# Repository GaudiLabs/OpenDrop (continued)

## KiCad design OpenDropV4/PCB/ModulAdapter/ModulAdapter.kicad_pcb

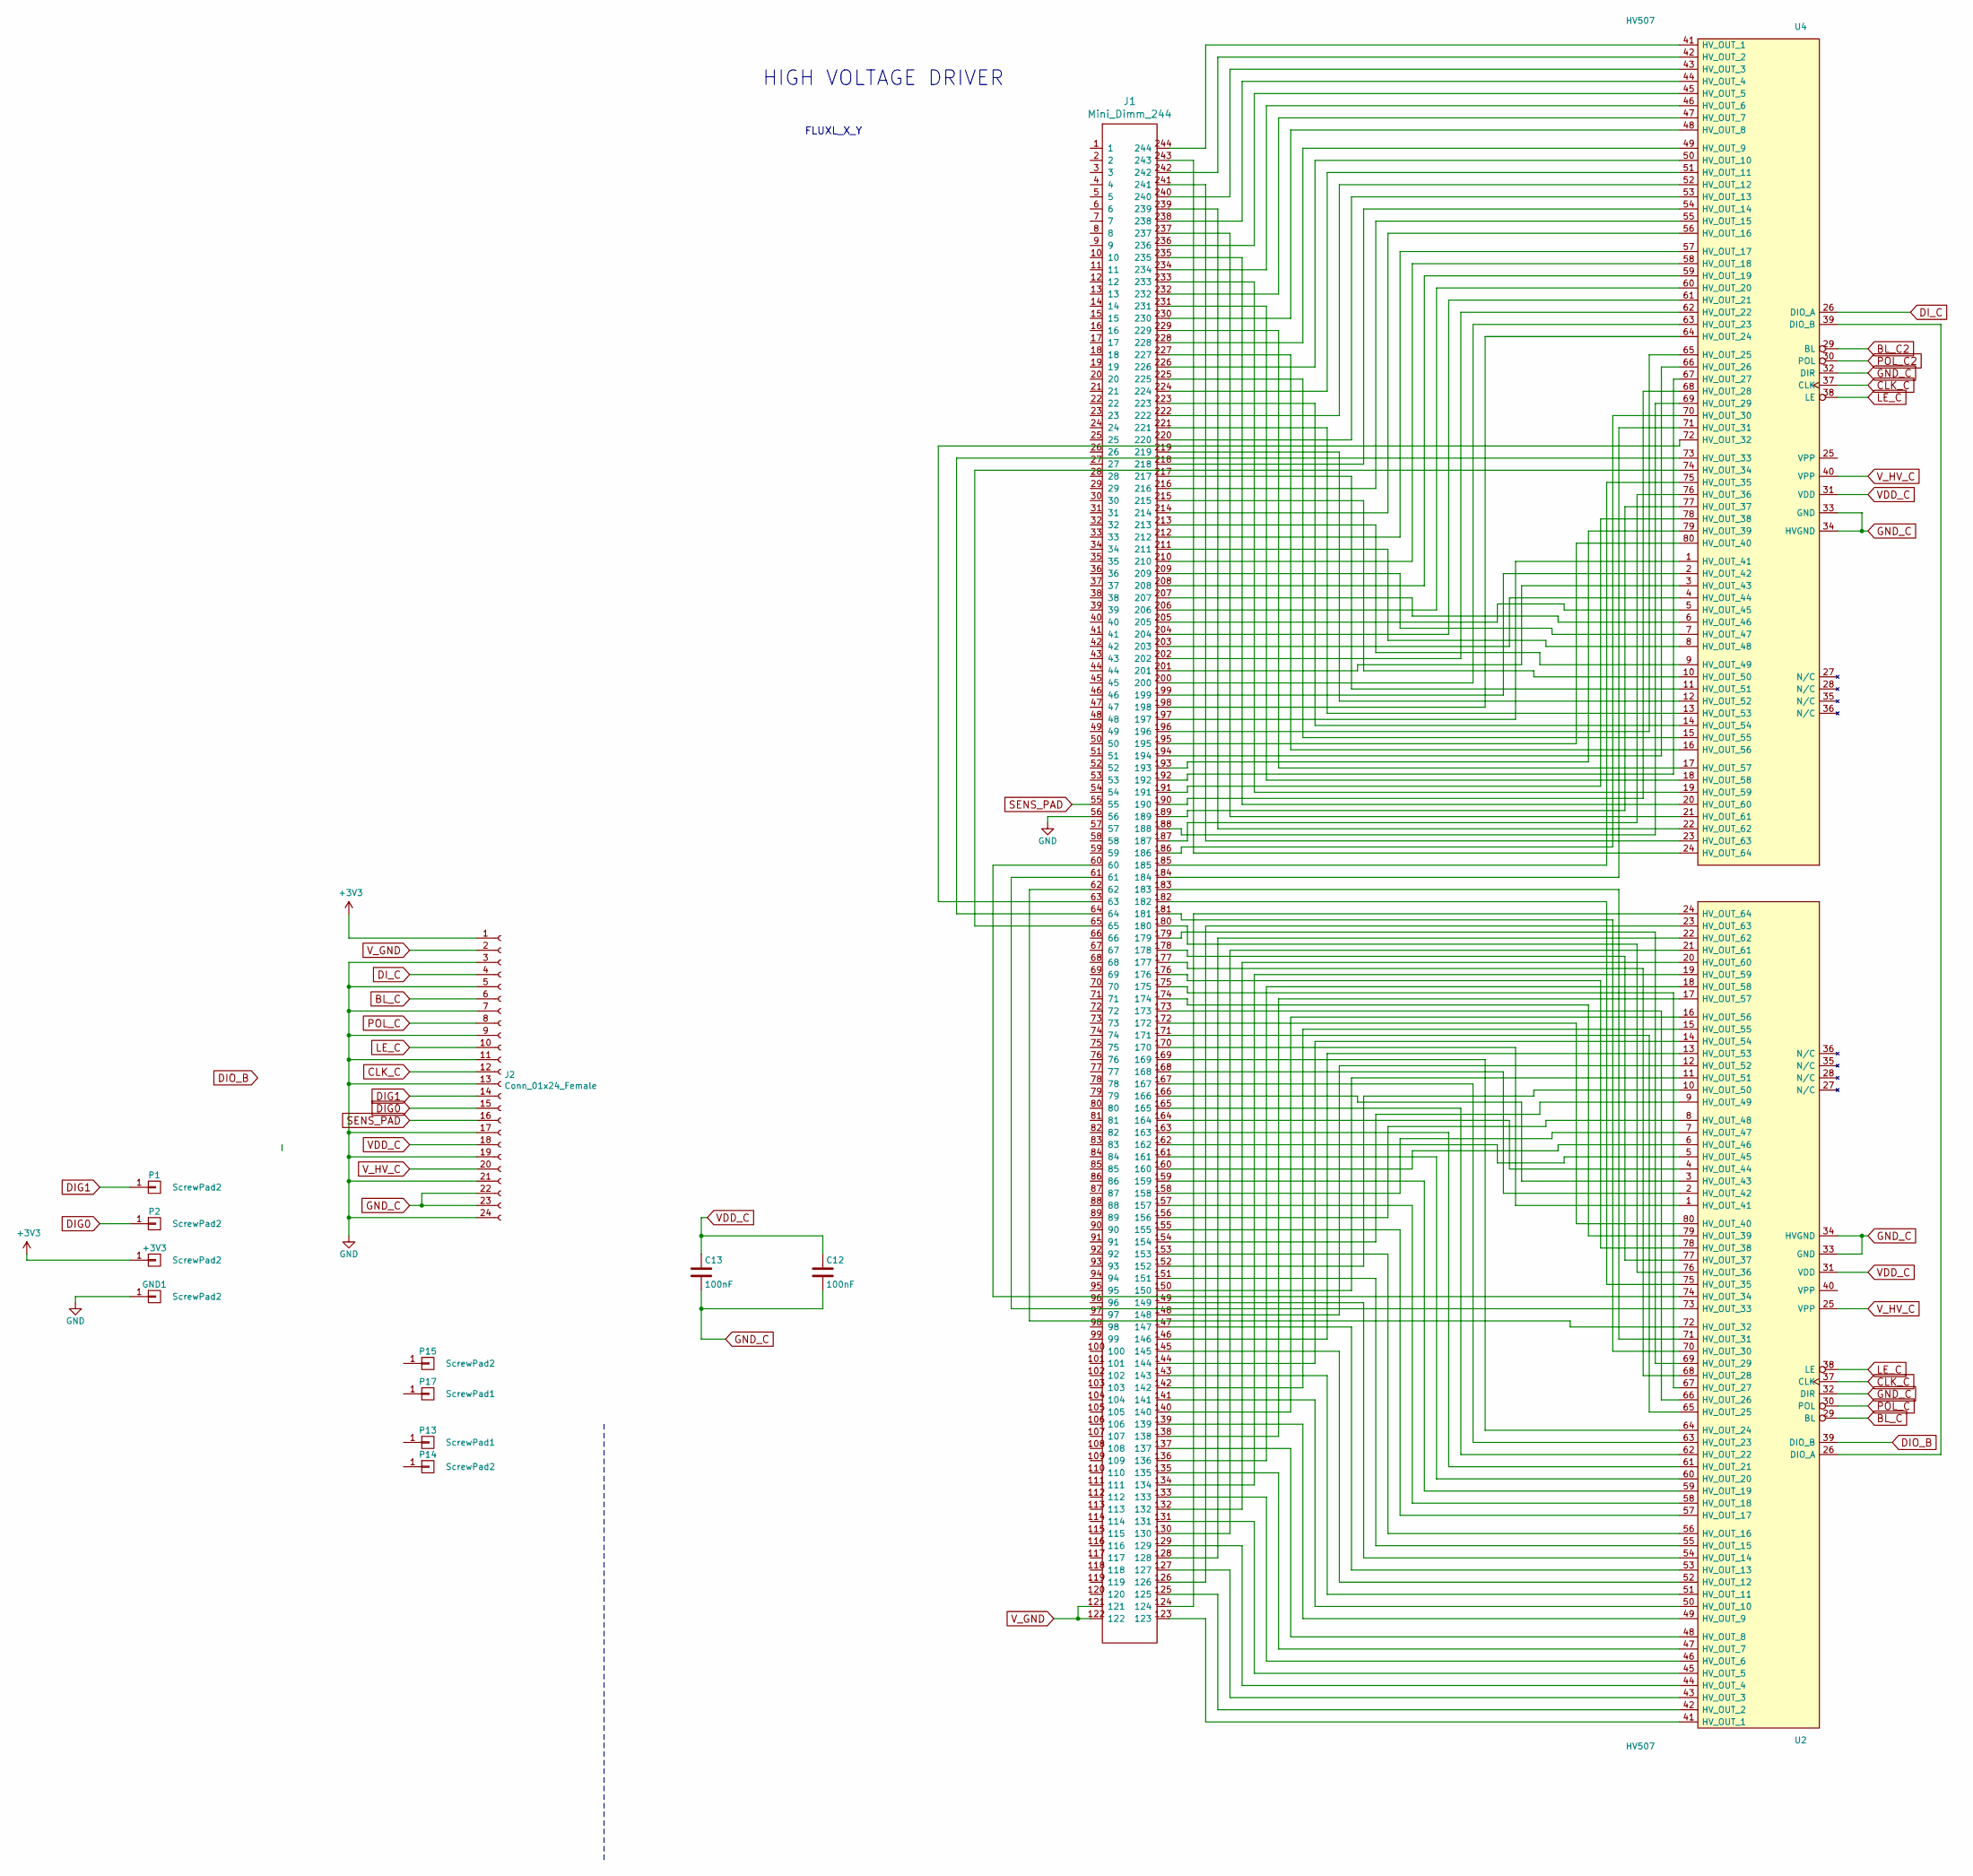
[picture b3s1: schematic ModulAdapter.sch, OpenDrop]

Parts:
+3V3: ScrewPad2; Measurement_Point_Square-SMD-Pad_Small
C12, C13: 100nF; C_0805
GND1: ScrewPad2; Measurement_Point_Square-SMD-Pad_Small
J1: Mini_Dimm_244
J2: Conn_01x24_Female; FFC_MOLEX_EASYON_05mm_24
P1, P2: ScrewPad2; Measurement_Point_Square-SMD-Pad_Small
P13, P17: ScrewPad1; MountingHoleM3
P14, P15: ScrewPad2; MountingHoleM3
U2, U4: HV507; PQFP-80_14x20mm_Pitch0.8mm

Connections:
+3V3: +3V3.1, J2.1
CLK_C: J2.12, U2.37 (CLK), U4.37 (CLK)
DIG0: J2.15, P2.1
DIG1: J2.14, P1.1
DI_C: J2.4, U4.26 (DIO_A)
GND: GND1.1, J1.56, J2.3, J2.5, J2.7, J2.9, J2.11, J2.13, J2.17, J2.19, J2.21, J2.24; also elsewhere on the board
GND_C: C12.2, C13.2, J2.22, J2.23, U2.32 (DIR), U2.33 (GND), U2.34 (HVGND), U4.32 (DIR), U4.33 (GND), U4.34 (HVGND)
LE_C: J2.10, U2.38 (LE), U4.38 (LE)
unnamed: J1.60, U2.74 (HV_OUT_34)
unnamed: J1.61, U2.73 (HV_OUT_33)
unnamed: J1.62, U2.72 (HV_OUT_32)
unnamed: J1.63, U4.72 (HV_OUT_32)
unnamed: J1.64, U4.73 (HV_OUT_33)
unnamed: J1.65, U4.74 (HV_OUT_34)
unnamed: J1.123, U2.41 (HV_OUT_1)
unnamed: J1.124, U2.24 (HV_OUT_64)
unnamed: J1.125, U2.42 (HV_OUT_2)
unnamed: J1.126, U2.23 (HV_OUT_63)
unnamed: J1.127, U2.43 (HV_OUT_3)
unnamed: J1.128, U2.22 (HV_OUT_62)
unnamed: J1.129, U2.44 (HV_OUT_4)
unnamed: J1.130, U2.21 (HV_OUT_61)
unnamed: J1.131, U2.45 (HV_OUT_5)
unnamed: J1.132, U2.20 (HV_OUT_60)
unnamed: J1.133, U2.46 (HV_OUT_6)
unnamed: J1.134, U2.19 (HV_OUT_59)
unnamed: J1.135, U2.47 (HV_OUT_7)
unnamed: J1.136, U2.18 (HV_OUT_58)
unnamed: J1.137, U2.48 (HV_OUT_8)
unnamed: J1.138, U2.17 (HV_OUT_57)
unnamed: J1.139, U2.49 (HV_OUT_9)
unnamed: J1.140, U2.16 (HV_OUT_56)
unnamed: J1.141, U2.50 (HV_OUT_10)
unnamed: J1.142, U2.15 (HV_OUT_55)
unnamed: J1.143, U2.51 (HV_OUT_11)
unnamed: J1.144, U2.14 (HV_OUT_54)
unnamed: J1.145, U2.52 (HV_OUT_12)
unnamed: J1.146, U2.13 (HV_OUT_53)
unnamed: J1.147, U2.53 (HV_OUT_13)
unnamed: J1.148, U2.12 (HV_OUT_52)
unnamed: J1.149, U2.54 (HV_OUT_14)
unnamed: J1.150, U2.11 (HV_OUT_51)
unnamed: J1.151, U2.55 (HV_OUT_15)
unnamed: J1.152, U2.10 (HV_OUT_50)
unnamed: J1.153, U2.56 (HV_OUT_16)
unnamed: J1.154, U2.9 (HV_OUT_49)
unnamed: J1.155, U2.57 (HV_OUT_17)
unnamed: J1.156, U2.8 (HV_OUT_48)
unnamed: J1.157, U2.58 (HV_OUT_18)
unnamed: J1.158, U2.7 (HV_OUT_47)
unnamed: J1.159, U2.59 (HV_OUT_19)
unnamed: J1.160, U2.6 (HV_OUT_46)
unnamed: J1.161, U2.60 (HV_OUT_20)
unnamed: J1.162, U2.5 (HV_OUT_45)
unnamed: J1.163, U2.61 (HV_OUT_21)
unnamed: J1.164, U2.4 (HV_OUT_44)
unnamed: J1.165, U2.62 (HV_OUT_22)
unnamed: J1.166, U2.3 (HV_OUT_43)
unnamed: J1.167, U2.63 (HV_OUT_23)
unnamed: J1.168, U2.2 (HV_OUT_42)
unnamed: J1.169, U2.64 (HV_OUT_24)
unnamed: J1.170, U2.1 (HV_OUT_41)
unnamed: J1.171, U2.65 (HV_OUT_25)
unnamed: J1.172, U2.80 (HV_OUT_40)
unnamed: J1.173, U2.66 (HV_OUT_26)
unnamed: J1.174, U2.79 (HV_OUT_39)
unnamed: J1.175, U2.67 (HV_OUT_27)
unnamed: J1.176, U2.78 (HV_OUT_38)
unnamed: J1.177, U2.68 (HV_OUT_28)
unnamed: J1.178, U2.77 (HV_OUT_37)
unnamed: J1.179, U2.69 (HV_OUT_29)
unnamed: J1.180, U2.76 (HV_OUT_36)
unnamed: J1.181, U2.70 (HV_OUT_30)
unnamed: J1.182, U2.75 (HV_OUT_35)
unnamed: J1.183, U2.71 (HV_OUT_31)
unnamed: J1.184, U4.71 (HV_OUT_31)
unnamed: J1.185, U4.75 (HV_OUT_35)
unnamed: J1.186, U4.70 (HV_OUT_30)
unnamed: J1.187, U4.76 (HV_OUT_36)
unnamed: J1.188, U4.69 (HV_OUT_29)
unnamed: J1.189, U4.77 (HV_OUT_37)
unnamed: J1.190, U4.68 (HV_OUT_28)
unnamed: J1.191, U4.78 (HV_OUT_38)
unnamed: J1.192, U4.67 (HV_OUT_27)
unnamed: J1.193, U4.79 (HV_OUT_39)
unnamed: J1.194, U4.66 (HV_OUT_26)
unnamed: J1.195, U4.80 (HV_OUT_40)
unnamed: J1.196, U4.65 (HV_OUT_25)
unnamed: J1.197, U4.1 (HV_OUT_41)
unnamed: J1.198, U4.64 (HV_OUT_24)
unnamed: J1.199, U4.2 (HV_OUT_42)
unnamed: J1.200, U4.63 (HV_OUT_23)
unnamed: J1.201, U4.3 (HV_OUT_43)
unnamed: J1.202, U4.62 (HV_OUT_22)
unnamed: J1.203, U4.4 (HV_OUT_44)
unnamed: J1.204, U4.61 (HV_OUT_21)
unnamed: J1.205, U4.5 (HV_OUT_45)
unnamed: J1.206, U4.60 (HV_OUT_20)
unnamed: J1.207, U4.6 (HV_OUT_46)
unnamed: J1.208, U4.59 (HV_OUT_19)
unnamed: J1.209, U4.7 (HV_OUT_47)
unnamed: J1.210, U4.58 (HV_OUT_18)
unnamed: J1.211, U4.8 (HV_OUT_48)
unnamed: J1.212, U4.57 (HV_OUT_17)
unnamed: J1.213, U4.9 (HV_OUT_49)
unnamed: J1.214, U4.56 (HV_OUT_16)
unnamed: J1.215, U4.10 (HV_OUT_50)
unnamed: J1.216, U4.55 (HV_OUT_15)
unnamed: J1.217, U4.11 (HV_OUT_51)
unnamed: J1.218, U4.54 (HV_OUT_14)
unnamed: J1.219, U4.12 (HV_OUT_52)
unnamed: J1.220, U4.53 (HV_OUT_13)
unnamed: J1.221, U4.13 (HV_OUT_53)
unnamed: J1.222, U4.52 (HV_OUT_12)
unnamed: J1.223, U4.14 (HV_OUT_54)
unnamed: J1.224, U4.51 (HV_OUT_11)
unnamed: J1.225, U4.15 (HV_OUT_55)
unnamed: J1.226, U4.50 (HV_OUT_10)
unnamed: J1.227, U4.16 (HV_OUT_56)
unnamed: J1.228, U4.49 (HV_OUT_9)
unnamed: J1.229, U4.17 (HV_OUT_57)
unnamed: J1.230, U4.48 (HV_OUT_8)
unnamed: J1.231, U4.18 (HV_OUT_58)
unnamed: J1.232, U4.47 (HV_OUT_7)
unnamed: J1.233, U4.19 (HV_OUT_59)
unnamed: J1.234, U4.46 (HV_OUT_6)
unnamed: J1.235, U4.20 (HV_OUT_60)
unnamed: J1.236, U4.45 (HV_OUT_5)
unnamed: J1.237, U4.21 (HV_OUT_61)
unnamed: J1.238, U4.44 (HV_OUT_4)
unnamed: J1.239, U4.22 (HV_OUT_62)
unnamed: J1.240, U4.43 (HV_OUT_3)
unnamed: J1.241, U4.23 (HV_OUT_63)
unnamed: J1.242, U4.42 (HV_OUT_2)
unnamed: J1.243, U4.24 (HV_OUT_64)
unnamed: J1.244, U4.41 (HV_OUT_1)
unnamed: U2.26 (DIO_A), U4.39 (DIO_B)
SENS_PAD: J1.55, J2.16
VDD_C: C12.1, C13.1, J2.18, U2.31 (VDD), U4.31 (VDD)
V_GND: J1.121, J1.122, J2.2
V_HV_C: J2.20, U2.25 (VPP), U4.40 (VPP)

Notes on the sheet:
HIGH VOLTAGE DRIVER
FLUXL_X_Y

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
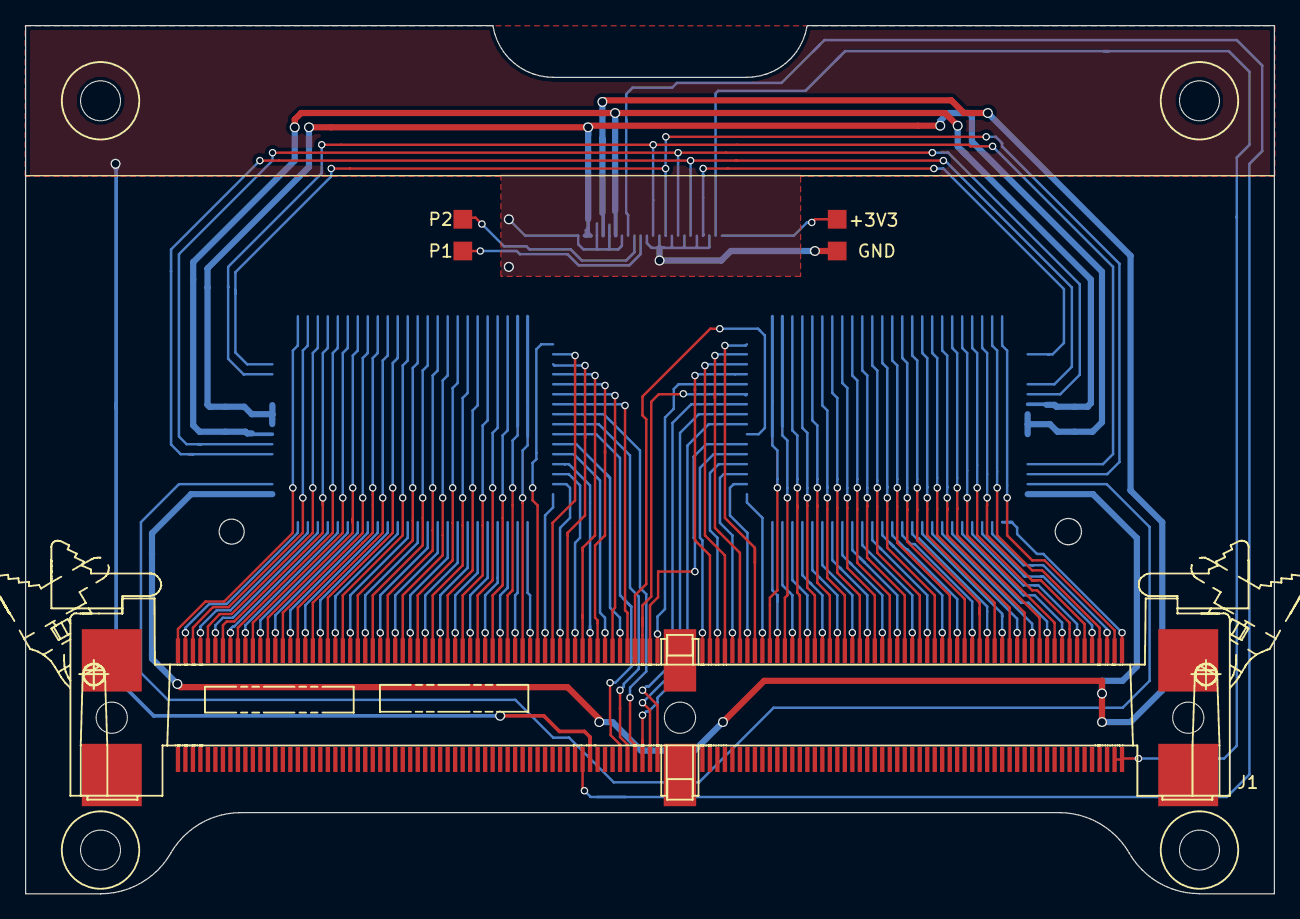
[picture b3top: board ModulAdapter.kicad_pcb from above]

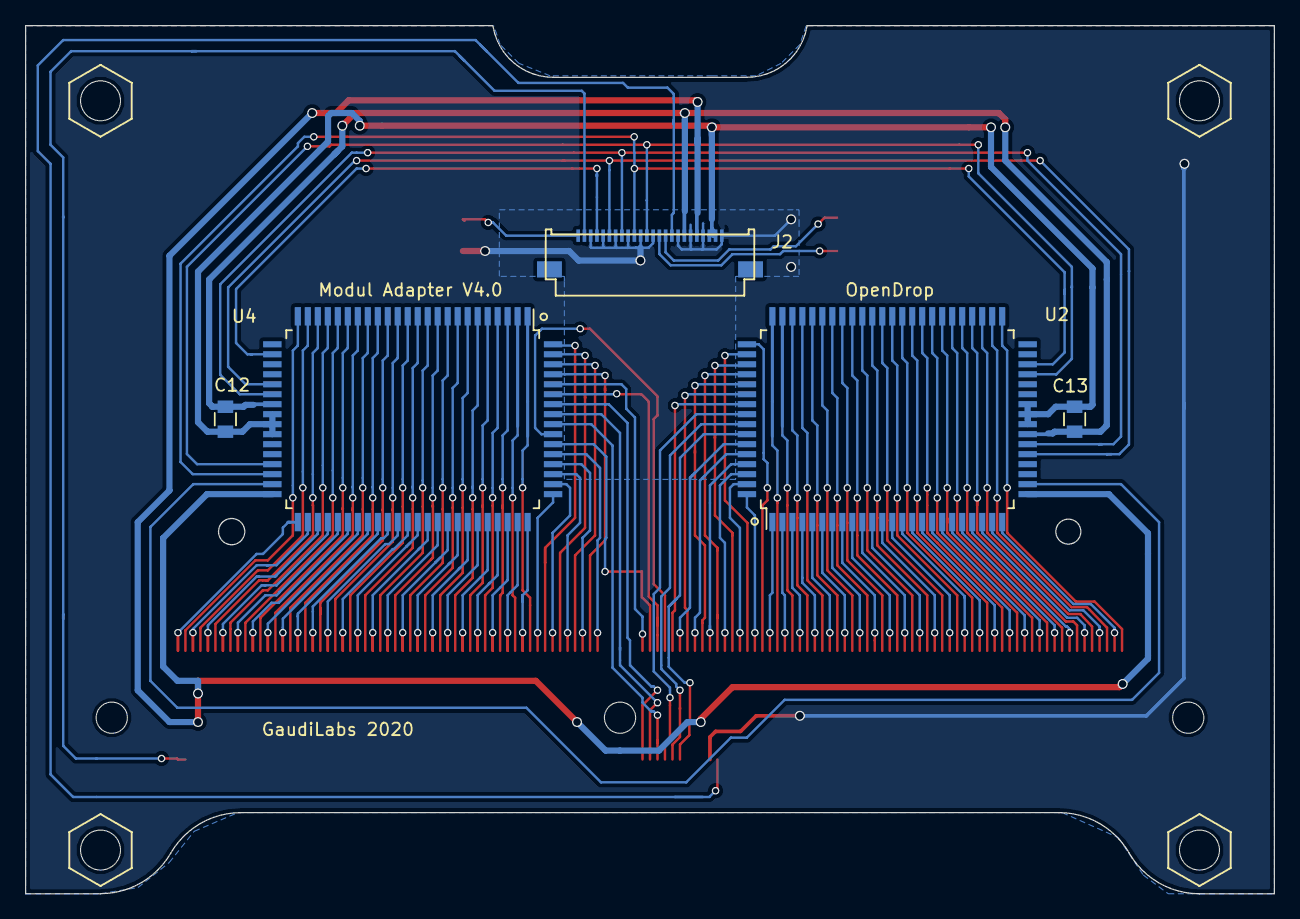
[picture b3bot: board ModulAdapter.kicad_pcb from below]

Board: 2 copper layers, 100.0 x 69.5 mm, 14 parts (5 on the bottom side), 143 nets.

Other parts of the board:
GND: ScrewPad2; Measurement_Point_Square-SMD-Pad_Small

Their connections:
GND: GND.1; also elsewhere on the board
